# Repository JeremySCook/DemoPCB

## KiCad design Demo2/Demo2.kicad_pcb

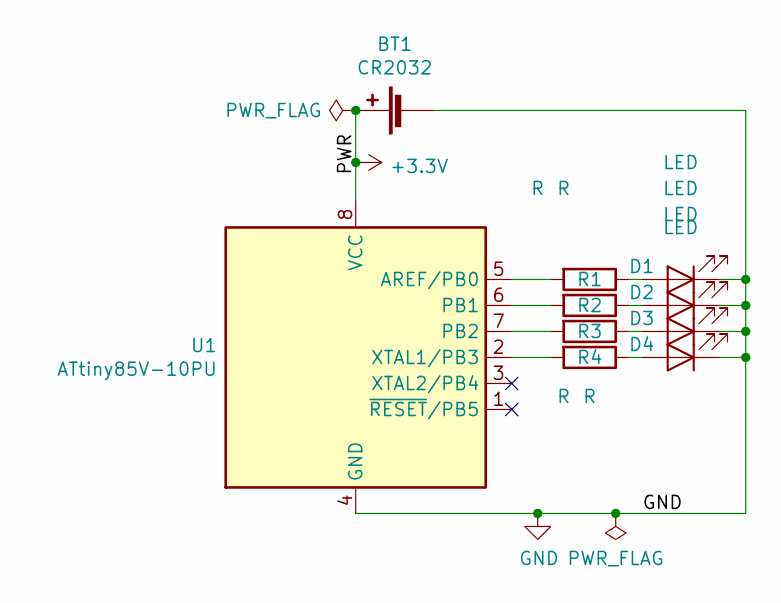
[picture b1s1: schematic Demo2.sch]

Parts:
BT1: CR2032; Battery_Panasonic_CR2032-VS1N_Vertical_CircularHoles
D1, D2, D3, D4: LED; LED_D3.0mm_Horizontal_O1.27mm_Z2.0mm
R1, R2, R3, R4: R; R_Axial_DIN0204_L3.6mm_D1.6mm_P5.08mm_Horizontal
U1: ATtiny85V-10PU; DIP-8_W7.62mm

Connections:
+3V3: BT1.1 (+), U1.8 (VCC)
GND: BT1.2 (-), D1.1 (K), D2.1 (K), D3.1 (K), D4.1 (K), U1.4 (GND)
unnamed: D1.2 (A), R1.1
unnamed: D2.2 (A), R2.1
unnamed: D3.2 (A), R3.1
unnamed: D4.2 (A), R4.1
unnamed: R1.2, U1.5 (AREF/PB0)
unnamed: R2.2, U1.6 (PB1)
unnamed: R3.2, U1.7 (PB2)
unnamed: R4.2, U1.2 (XTAL1/PB3)

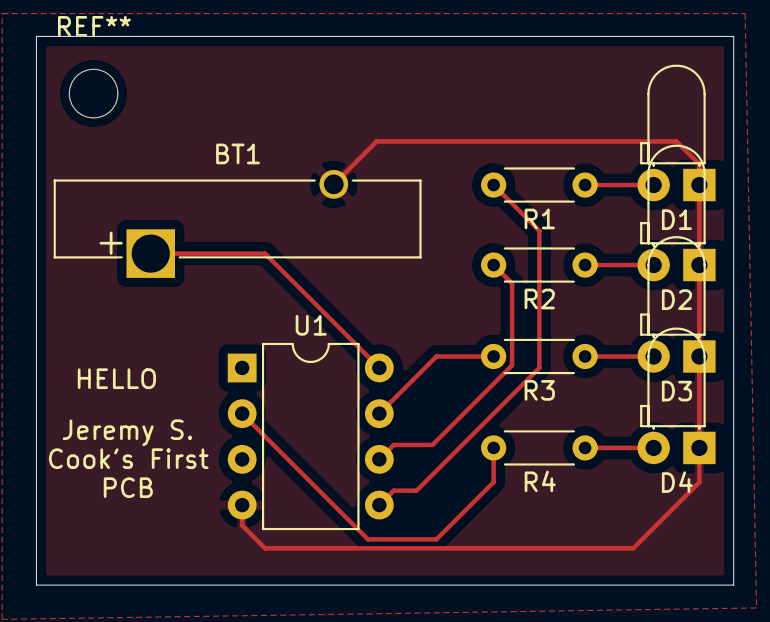
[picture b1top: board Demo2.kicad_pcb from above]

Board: 2 copper layers, 38.7 x 30.5 mm, 10 parts (0 on the bottom side), 10 nets.
